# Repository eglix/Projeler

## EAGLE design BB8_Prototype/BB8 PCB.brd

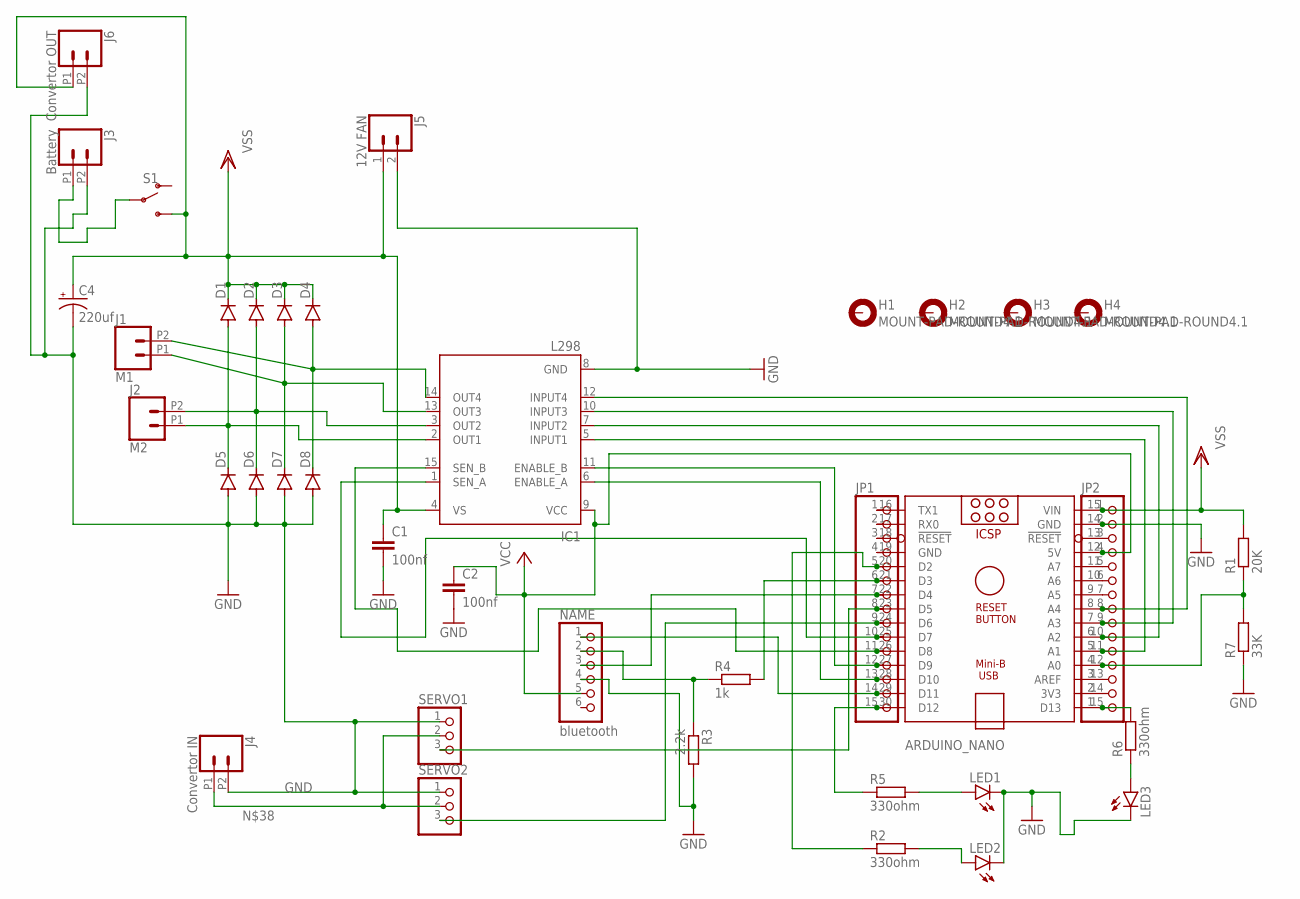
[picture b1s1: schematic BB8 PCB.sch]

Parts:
ARDUINO_NANO: ARDUINO_NANO
BLUETOOTH: bluetooth; 1X06
C1, C2: 100nf; C5B2.5
C4: 220uf; E5-8,5
D1, D2, D3, D4, D5, D6, D7, D8: 1N4148DO35-7; DO35-7
H1, H2, H3, H4: MOUNT-PAD-ROUND4.1; 4,1-PAD
IC1: L298; MULTIWATT-15
J1: M1; 1X02_2.54_SCREWTERM
J2: M2; 1X02_2.54_SCREWTERM
J3: Battery; 1X02_2.54_SCREWTERM
J4: Convertor IN; 1X02_2.54_SCREWTERM
J5: 12V FAN; 1X02
J6: Convertor OUT; 1X02_2.54_SCREWTERM
JP1, JP2: PINHD-1X15; 1X15
LED1, LED2, LED3: LED5MM
R1: 20K; 0204/7
R2, R5, R6: 330ohm; 0204/7
R3: 2.2k; 0204/7
R4: 1k; 0204/7
R7: 33K; 0204/7
S1: SWITCH-SPDT-PTH-11.6X4.0MM-LOCK; SWITCH_SPDT_PTH_11.6X4.0MM_LOCK
SERVO1, SERVO2: PINHD-1X3; 1X03

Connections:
12V: ARDUINO_NANO.15 (VIN), C1.1, C4.+, D1.C, D2.C, D3.C, D4.C, IC1.4 (VS), J5.1, J6.P1 (1), JP2.1, R1.2, S1.3 (S)
GND: ARDUINO_NANO.14 (GND), BLUETOOTH.4, C1.2, C2.2, C4.-, D5.A, D6.A, D7.A, D8.A, IC1.8 (GND), J3.P2 (2), J4.P2 (2), J5.2, J6.P2 (2), JP2.2, LED1.K (C), LED2.K (C), LED3.K (C), R3.2, R7.1, SERVO1.1, SERVO2.1
unnamed: ARDUINO_NANO.21 (D3), JP1.6, R4.2
unnamed: BLUETOOTH.2, R3.1, R4.1
unnamed: ARDUINO_NANO.22 (D4), BLUETOOTH.3, JP1.7
unnamed: ARDUINO_NANO.29 (D11), BLUETOOTH.1, JP1.14
unnamed: ARDUINO_NANO.23 (D5), JP1.8, SERVO1.3
unnamed: ARDUINO_NANO.24 (D6), JP1.9, SERVO2.3
unnamed: ARDUINO_NANO.28 (D10), IC1.6 (ENABLE_A), JP1.13
unnamed: ARDUINO_NANO.6 (A2), IC1.7 (INPUT2), JP2.10
unnamed: ARDUINO_NANO.5 (A1), IC1.5 (INPUT1), JP2.11
unnamed: ARDUINO_NANO.8 (A4), IC1.12 (INPUT4), JP2.8
unnamed: D1.A, D5.C, IC1.2 (OUT1), J2.P1 (1)
unnamed: D2.A, D6.C, IC1.3 (OUT2), J2.P2 (2)
unnamed: ARDUINO_NANO.25 (D7), IC1.1 (SEN_A), JP1.10
unnamed: D3.A, D7.C, IC1.13 (OUT3), J1.P1 (1)
unnamed: D4.A, D8.C, IC1.14 (OUT4), J1.P2 (2)
unnamed: ARDUINO_NANO.30 (D12), JP1.15, R5.1
unnamed: LED1.A, R5.2
unnamed: LED2.A, R2.2
unnamed: ARDUINO_NANO.20 (D2), JP1.5, R2.1
unnamed: ARDUINO_NANO.1 (D13), JP2.15, R6.2
unnamed: LED3.A, R6.1
unnamed: ARDUINO_NANO.27 (D9), IC1.11 (ENABLE_B), JP1.12
unnamed: ARDUINO_NANO.7 (A3), IC1.10 (INPUT3), JP2.9
unnamed: ARDUINO_NANO.26 (D8), IC1.15 (SEN_B), JP1.11
unnamed: ARDUINO_NANO.4 (A0), JP2.12, R1.1, R7.2
unnamed: ARDUINO_NANO.16 (TX1), JP1.1
unnamed: ARDUINO_NANO.17 (RX0), JP1.2
unnamed: ARDUINO_NANO.18 (!RESET), JP1.3
unnamed: ARDUINO_NANO.19 (GND), JP1.4
unnamed: ARDUINO_NANO.13 (!RESET), JP2.3
unnamed: ARDUINO_NANO.11 (A7), JP2.5
unnamed: ARDUINO_NANO.10 (A6), JP2.6
unnamed: ARDUINO_NANO.9 (A5), JP2.7
unnamed: ARDUINO_NANO.3 (AREF), JP2.13
unnamed: ARDUINO_NANO.2 (3V3), JP2.14
unnamed: J3.P1 (1), S1.2
unnamed: J4.P1 (1), SERVO1.2, SERVO2.2
VCC: ARDUINO_NANO.12 (5V), BLUETOOTH.5, C2.1, IC1.9 (VCC), JP2.4

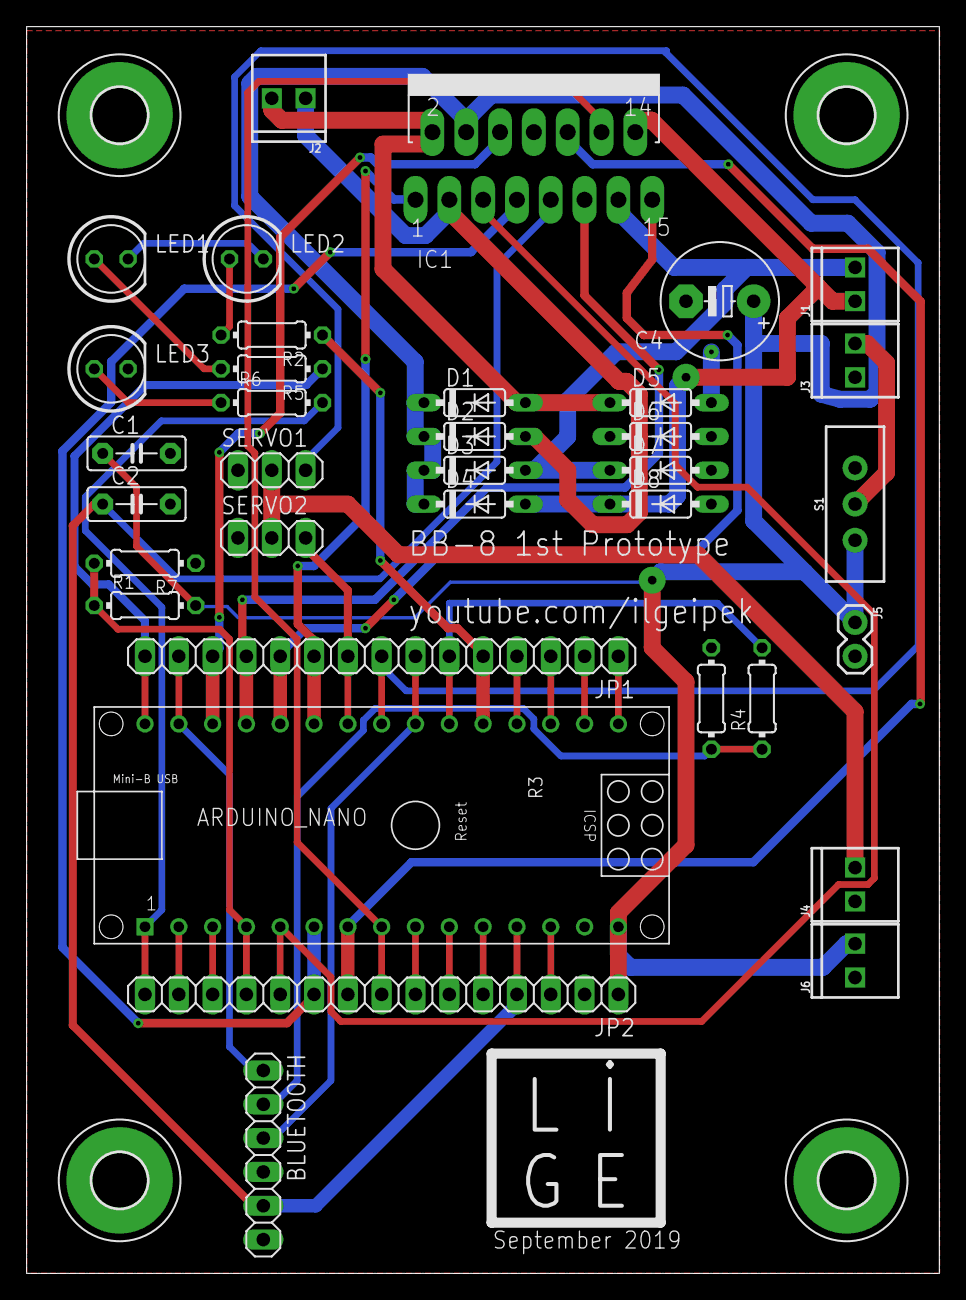
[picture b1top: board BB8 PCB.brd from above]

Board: 2 copper layers, 68.6 x 93.7 mm, 39 parts (0 on the bottom side), 40 nets.

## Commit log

2019-04-22 Create Video Link
2019-12-02 Create Link
2019-12-05 Update Link
2020-06-14 Create videolink
2020-06-20 Create Video_Link
2020-11-21 Create blank
2020-12-19 Create Video
2022-03-05 Update video_link
2022-03-05 Create STLs
2022-03-05 Create Baglantılar

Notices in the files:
parts and their libraries:
SparkFun-Connectors: Licensing: Creative Commons ShareAlike 4.0 International - https://creativecommons.org/licenses/by-sa/4.0
